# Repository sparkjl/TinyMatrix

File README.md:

## TinyMatrix点阵控制器
> 基于STM32F103 Microcontroller，HUB75接口的点阵控制器。可通过1 x 4按键、串口指令控制LED点阵屏显示。

### 1. 硬件
#### 1.1. HUB75接口定义
Led点阵板的HUB75接口，一般以DC3-16P牛角座封装形式接入。通常Led点阵板的左右两侧各有一个HUB75接口IN、OUT，以实现多块Led点阵板的组合扩展。HUB75接口中：R1、G1、B1分别为上半屏的红、绿、蓝控制信号，R2、G2、B2分别为下半屏的红、绿、蓝控制信号，A、B、C、D、E为行选择信号，CLK为数据时钟信号，LAT为数据锁存信号，OE为输出使能信号，GND为信号地。

<div align="center">
    
</div>

#### 1.2. HUB75扫描方式
将行扫描信号、行选择信号进行组合控制，就实现了整个Led点阵板的扫描显示。其具体实现过程如下：

<div align="center">
    
</div>

1. 从DATA_IN引脚（R1、G1、B1、R2、G2、B2）写入1 bit数据，将CLK引脚拉高产生上升沿将数据写入移位寄存器。如此循环m次将一行m bit数据传输至移位寄存器。
2. 将LATCH、<SPAN style="TEXT-DECORATION: overline">OE</SPAN>引脚拉高，m bit数据被从移位寄存器传输至缓存寄存器。同时缓存寄存器中数据被保持禁止从输出驱动器中输出，以使得在行选择信号切换时没有Led被点亮。
3. 切换并输出行选择信号。(初始状态时，第0行、第32行被选中。)
4. 将LATCH、<SPAN style="TEXT-DECORATION: overline">OE</SPAN>引脚拉低，m bit数据被从缓存寄存器传输至输出驱动器。同时移位寄存器中数据被锁存禁止从缓存寄存器中移出，此时对应选中行Led被点亮。

将以上步骤执行n/2次，便能实现m x n像素Led点阵板整个画面的扫描显示。如果扫描频率足够低，我们能看到逐行扫描显示的全过程：

<div align="center">
    
</div>

基于人眼视觉暂留效应（余晖效应），我们无法分辨刷新率在24Hz以上的动态画面。如果将扫描频率设置在60Hz，我们就能看到一幅完整的静态画面。而这也就是常见的显示器的基本原理。

最后，将Led点阵板上下两个部分的R1、G1、B1、R2、G2、B2控制信号进行组合，便能基于光学RGB模型实现全彩显示。

#### 1.3. Led Matrix控制板设计
了解了HUB75接口的控制原理，接下来进行Led Matrix控制板设计。

Led Matrix控制板设计思路如下：

<div align="center">
    
</div>

Led Matrix控制板的核心选择的是一款尺寸为 22.86mm x 53.34mm 的STM32最小系统板。其通过2 x 20Pin GPIO排针将板载STM32F103C8T6 MCU内集成的2x SPI、3x USART、2x I2C、1x CAN、37x I/O、2x ADC、4x Timer等硬件资源引出，以便外围扩展板调用。固件程序可通过SWD接口进行烧录和调试，可通过Reset键复位。板载2路Led灯，一路用于电源状态指示，一路用于程序状态指示。

<div align="center">
    
</div>

Led Matrix控制板设计1 x 4按键用于点阵控制器的参数设置。MCU相关GPIO经由74HC245连接至HUB75接口，以增加驱动电流并将驱动电压从3.3v转换至5.0v。外挂的W25Qxx系列SPI Flash用于存储系统参数和字库数据。UART串口可用于下载系统参数和字库数据，TTL-蓝牙模块、TTL-WiFi模块通过UART串口建立与MCU间的通讯以实现控制指令、显示数据的无线透传。Led Matrix控制板由外接电源适配器或内置锂离子电池提供系统电源，直流降压电路实现系统电源从12v-> 5v-> 3.3v电压转换以给各功能单元供电。

基于以上硬件需求，将Led Matrix控制板通过Eagle PCB设计如下。至于为什么是Eagle PCB，那是因为其小巧精悍、简单易用，丰富的元件库、精美的原理图、标准vector字体，无不透露着严谨精致。可惜的是，被Autodesk收购后的Eagle 9.6.2对于3D模型的预览编辑需要通过Fusion 360来实现。

<div align="center">
    
</div>
<div align="center">
    
</div>

### 2. 结构

Eagle 9.6.2不支持直接编辑3D封装，而只能通过Fusion 360以云托管元件库的方式导入。不想从Fusion 360中重构元件库，但又追求项目完整性，这怎么解决呢？那就选择KiCad，不仅支持3D封装的直接编辑，还能将Eagle的.sch原理图文件、.brd电路板文件转换成对应的KiCad格式文件。

使用KiCad将Led Matrix控制板的Eagle格式文件转换成KiCad格式文件，基于此添加编辑3D封装，导出Led Matrix控制板3D Step模型文件。

使用KiCad对MCU核心板重新进行layout，添加编辑3D封装，导出MCU核心板3D Step模型文件。

在Fusion 360中将Led Matrix控制板和MCU核心板进行零件装配、干涉检查。

在Fusion 360中将Led Matrix控制板设置为固定零件，以此为基准依据Led Matrix控制板的空间尺寸设计Led Matrix控制器的整体结构。选择亚克力板材作为外壳材质。顶部和底部亚克力板通过双通螺母柱进行连接，Led Matrix控制板和Led点阵板与底部亚克力板连接固定，四侧亚克力板与顶部和底部亚克力板通过卡扣扣合进行连接。

### 3. 软件
#### 3.1. RGB LED全彩显示
控制RGB LED实现全彩显示的传统方式是脉宽调制（Pulse Width Modulation），简称PWM。通过脉宽调制控制LED开关时间占比，进而实现RGB LED的亮度调节。如果对RGB模块中的三个LED进行此操作，则可以将红绿蓝三色按比例混合成对应的RGB全彩输出。对于Led Matrix Panel的全彩显示，PWM方式却不适用：这需要足够多的GPIO和定时器独立控制，需要消耗太多的硬件资源。那么我们如何通过软件方式予以解决呢？  

二进制编码调制（Binary Code Modulation），简称BCM。BCM利用二进制编码性质控制开关信号占空比。假设有一个位宽为4的二进制数：从其最低位向左移动至最高位依次表示1个时间切片、2个时间切片、4个时间切片、8个时间切片。将这4种时间切片混合，可产生分辨率为1/15的任意占空比。如此，位宽越大分辨率越高色彩越丰富。位宽为8的二进制数，可表示分辨率为1/255的任意占空比。但位宽越大，时间切片越小，意味着更高的CPU占用率。为更好地平衡系统性能和硬件资源，本项目中BCM位宽为4。例如，4位二进制数0101表示5/15或33.3%的占空比。

<div align="center">
    
</div>

Led Matrix Panel是逐行扫描显示的，所以需要预先将图像像素色彩转换成BCM值保存至图像缓冲区。创建4个图像缓冲区，以表示BCM位宽为4情况下的4种长度的时间切片中在扫描时间范围内哪些时间切片需要点亮LED。将这4个图像缓冲区构成的4个颜色通道Plane，进行图像融合就构成了一幅完整的静态图像。

<div align="center">
    
</div>

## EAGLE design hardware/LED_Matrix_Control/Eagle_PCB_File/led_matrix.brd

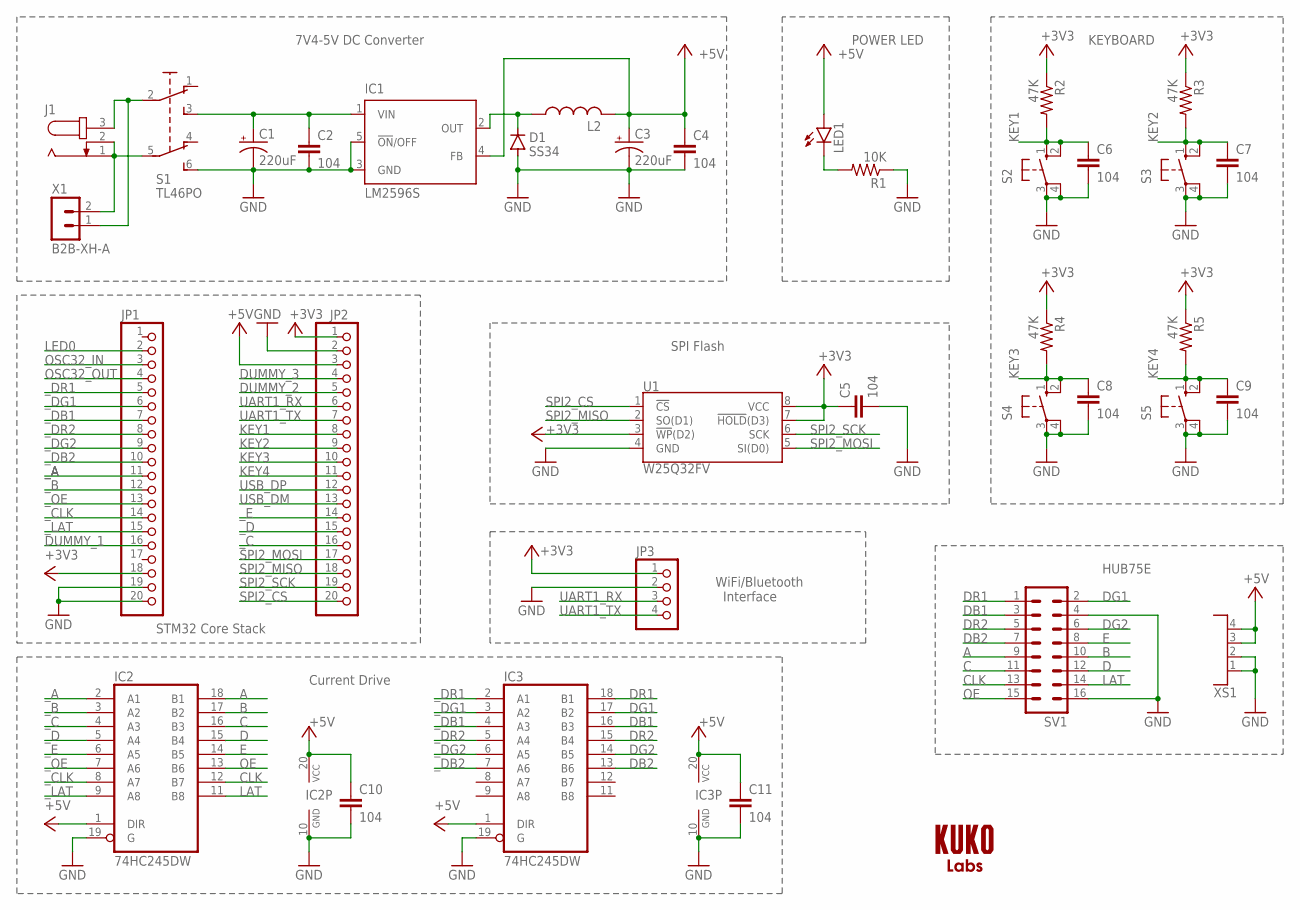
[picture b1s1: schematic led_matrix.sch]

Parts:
C1, C3: 220uF; 153CLV-0605
C2, C4, C5, C6, C7, C8, C9, C10, C11: 104; C0805
D1: SS34; DO214AC
IC1: LM2596S; TO263-5
IC2, IC3: 74HC245DW; SO20W
J1: JACK-PLUG0; SPC4077
JP1, JP2: PINHD-1X20; 1X20
JP3: PINHD-1X4; 1X04
L2: L-USL4532P; L4532P
LED1: LEDCHIP-LED0805; CHIP-LED0805
R1: 10K; R0805
R2, R3, R4, R5: 47K; R0805
S1: TL46PO; TL4XPO
S2, S3, S4, S5: 10-XX; B3F-10XX
SV1: ML16
U1: W25Q32FV; SOIC-8
U$1: LOGO
X1: B2B-XH-A
XS1: C4; NINIGI4C

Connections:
+3V3: C5.1, JP1.18, JP2.1, JP3.1, R2.1, R3.1, R4.1, R5.1, U1.3 (!WP!(D2)), U1.7 (!HOLD!(D3)), U1.8 (VCC)
+5V: C3.+, C4.1, C10.1, C11.1, IC1.4 (FB), IC2.1 (DIR), IC2.20 (VCC), IC3.1 (DIR), IC3.20 (VCC), JP2.3, L2.2, LED1.A, XS1.3, XS1.4
A: IC2.18 (B1), SV1.9
B: IC2.17 (B2), SV1.10
C: IC2.16 (B3), SV1.11
CLK: IC2.12 (B7), SV1.13
D: IC2.15 (B4), SV1.12
DB1: IC3.16 (B3), SV1.3
DB2: IC3.13 (B6), SV1.7
DG1: IC3.17 (B2), SV1.2
DG2: IC3.14 (B5), SV1.6
DR1: IC3.18 (B1), SV1.1
DR2: IC3.15 (B4), SV1.5
DUMMY_1: JP1.16
DUMMY_2: JP2.5
DUMMY_3: JP2.4
E: IC2.14 (B5), SV1.8
GND: C1.-, C2.2, C3.-, C4.2, C5.2, C6.2, C7.2, C8.2, C9.2, C10.2, C11.2, D1.A, IC1.3 (GND), IC1.5 (!ON!/OFF), IC2.10 (GND), IC2.19 (G), IC3.10 (GND), IC3.19 (G), JP1.19, JP1.20, JP2.2, JP3.2, R1.1, S1.6 (S1), S2.3, S2.4 (P1), S3.3, S3.4 (P1), S4.3, S4.4 (P1), S5.3, S5.4 (P1), SV1.4, SV1.16, U1.4 (GND), XS1.1, XS1.2
KEY1: C6.1, JP2.8, R2.2, S2.1 (S), S2.2 (S1)
KEY2: C7.1, JP2.9, R3.2, S3.1 (S), S3.2 (S1)
KEY3: C8.1, JP2.10, R4.2, S4.1 (S), S4.2 (S1)
KEY4: C9.1, JP2.11, R5.2, S5.1 (S), S5.2 (S1)
LAT: IC2.11 (B8), SV1.14
LED0: JP1.2
unnamed: J1.3, S1.2, X1.1
unnamed: J1.1, J1.2, S1.5 (P1), X1.2
unnamed: C1.+, C2.1, IC1.1 (VIN), S1.3 (S)
unnamed: D1.C, IC1.2 (OUT), L2.1
unnamed: LED1.C, R1.2
OE: IC2.13 (B6), SV1.15
OSC32_IN: JP1.3
OSC32_OUT: JP1.4
SPI2_CS: JP2.20, U1.1 (!CS!)
SPI2_MISO: JP2.18, U1.2 (SO(D1))
SPI2_MOSI: JP2.17, U1.5 (SI(D0))
SPI2_SCK: JP2.19, U1.6 (SCK)
UART1_RX: JP2.6, JP3.3
UART1_TX: JP2.7, JP3.4
USB_DM: JP2.13
USB_DP: JP2.12
_A: IC2.2 (A1), JP1.11
_B: IC2.3 (A2), JP1.12
_C: IC2.4 (A3), JP2.16
_CLK: IC2.8 (A7), JP1.14
_D: IC2.5 (A4), JP2.15
_DB1: IC3.4 (A3), JP1.7
_DB2: IC3.7 (A6), JP1.10
_DG1: IC3.3 (A2), JP1.6
_DG2: IC3.6 (A5), JP1.9
_DR1: IC3.2 (A1), JP1.5
_DR2: IC3.5 (A4), JP1.8
_E: IC2.6 (A5), JP2.14
_LAT: IC2.9 (A8), JP1.15
_OE: IC2.7 (A6), JP1.13

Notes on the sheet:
POWER LED
7V4-5V DC Converter
KEYBOARD
HUB75E
SPI Flash
STM32 Core Stack
Current Drive
WiFi/Bluetooth Interface

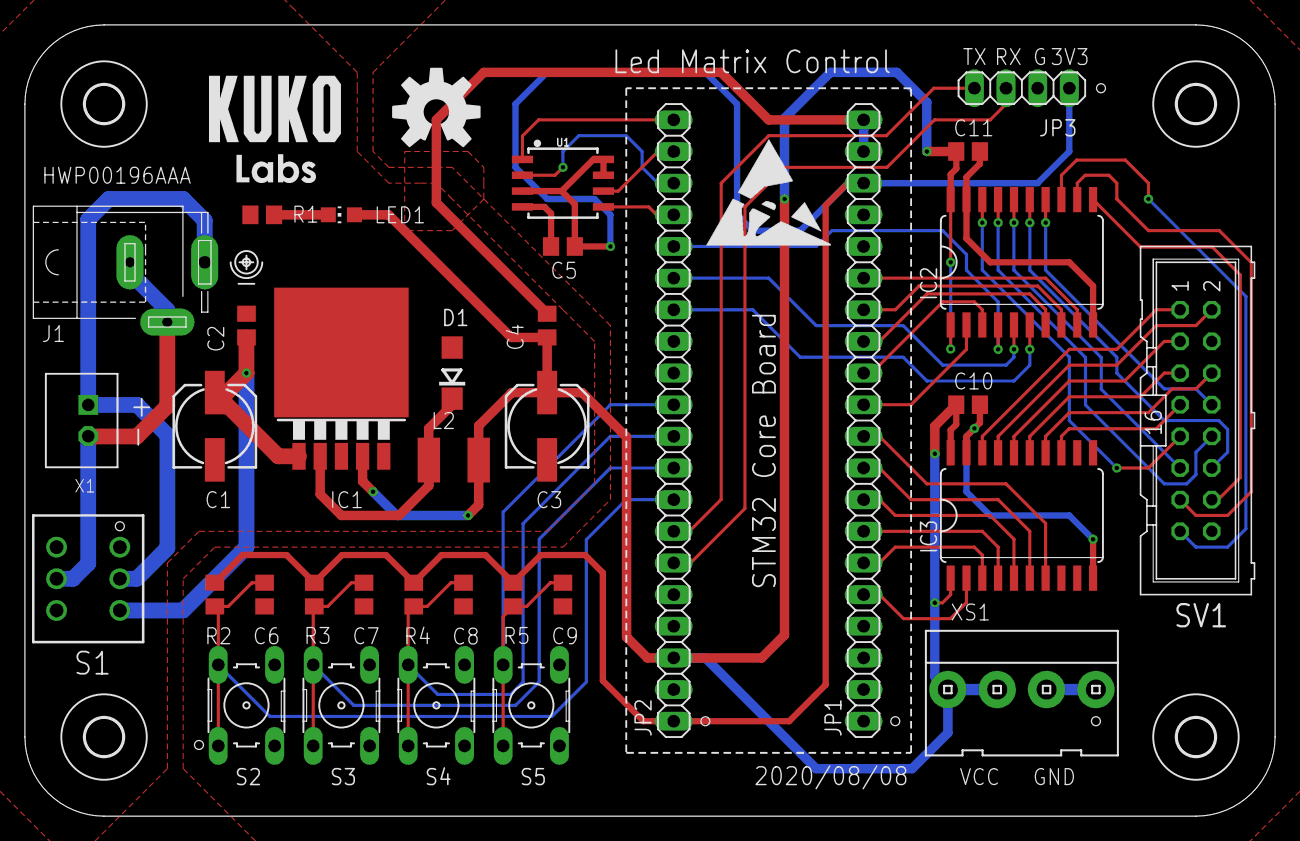
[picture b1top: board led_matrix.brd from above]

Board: 2 copper layers, 100.3 x 63.5 mm, 42 parts (0 on the bottom side), 46 nets.

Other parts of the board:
U$2, U$3, U$4, U$5: 3,0
U$6: ESD_10.00
U$7: OSHW-LOGO-L

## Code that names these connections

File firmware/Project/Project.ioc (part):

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Mcu.Name=STM32F103C(8-B)Tx
Mcu.Package=LQFP48
Mcu.UserName=STM32F103C8Tx
PA0-WKUP.GPIOParameters=GPIO_Label
PA0-WKUP.GPIO_Label=HUB75_DR1
PA0-WKUP.Signal=GPIO_Output
PA1.GPIOParameters=GPIO_Label
PA1.GPIO_Label=HUB75_DG1
PA1.Signal=GPIO_Output
PA10.GPIOParameters=GPIO_Label
PA10.GPIO_Label=HUB75_E
PA10.Signal=GPIO_Output
PA11.Mode=Device
PA11.Signal=USB_DM
PA12.Mode=Device
PA12.Signal=USB_DP
PA13.Mode=Serial_Wire
PA13.Signal=SYS_JTMS-SWDIO
PA14.Mode=Serial_Wire
PA14.Signal=SYS_JTCK-SWCLK
PA15.GPIOParameters=GPIO_Label
PA15.GPIO_Label=KEY_4
PA15.Signal=GPIO_Input
PA2.GPIOParameters=GPIO_Label
PA2.GPIO_Label=HUB75_DB1
PA2.Signal=GPIO_Output
PA3.GPIOParameters=GPIO_Label
PA3.GPIO_Label=HUB75_DR2
PA3.Signal=GPIO_Output
PA4.GPIOParameters=GPIO_Label
PA4.GPIO_Label=HUB75_DG2
PA4.Signal=GPIO_Output
PA5.GPIOParameters=GPIO_Label
PA5.GPIO_Label=HUB75_DB2
PA5.Signal=GPIO_Output
PA6.GPIOParameters=GPIO_Label
PA6.GPIO_Label=HUB75_A
PA6.Signal=GPIO_Output
PA7.GPIOParameters=GPIO_Label
PA7.GPIO_Label=HUB75_B
PA7.Signal=GPIO_Output
PA8.GPIOParameters=GPIO_Label
PA8.GPIO_Label=HUB75_C
PA8.Signal=GPIO_Output
PA9.GPIOParameters=GPIO_Label
PA9.GPIO_Label=HUB75_D
PA9.Signal=GPIO_Output
PB0.GPIOParameters=GPIO_Label
PB0.GPIO_Label=HUB75_OE
PB0.Signal=GPIO_Output
PB1.GPIOParameters=GPIO_Label
PB1.GPIO_Label=HUB75_CLK
PB1.Signal=GPIO_Output
PB10.GPIOParameters=GPIO_Label
PB10.GPIO_Label=HUB75_LAT
PB10.Signal=GPIO_Output
PB12.GPIOParameters=GPIO_Speed,PinState,GPIO_Label
PB12.GPIO_Label=SPI2_CS
PB12.GPIO_Speed=GPIO_SPEED_FREQ_HIGH
PB12.PinState=GPIO_PIN_SET
PB12.Signal=GPIO_Output
PB13.Mode=Full_Duplex_Master
PB13.Signal=SPI2_SCK
PB14.Mode=Full_Duplex_Master
PB14.Signal=SPI2_MISO
PB15.Mode=Full_Duplex_Master
PB15.Signal=SPI2_MOSI
PB3.GPIOParameters=GPIO_Label
PB3.GPIO_Label=KEY_3
PB3.Signal=GPIO_Input
PB4.GPIOParameters=GPIO_Label
PB4.GPIO_Label=KEY_2
PB4.Signal=GPIO_Input
PB5.GPIOParameters=GPIO_Label
PB5.GPIO_Label=KEY_1
PB5.Signal=GPIO_Input
PB6.Mode=Asynchronous
PB6.Signal=USART1_TX
PB7.Mode=Asynchronous
PB7.Signal=USART1_RX
PC13-TAMPER-RTC.GPIOParameters=GPIO_Label
PC13-TAMPER-RTC.GPIO_Label=LED1
PC13-TAMPER-RTC.Signal=GPIO_Output
PC14-OSC32_IN.Mode=LSE-External-Oscillator
PC14-OSC32_IN.Signal=RCC_OSC32_IN
PC15-OSC32_OUT.Mode=LSE-External-Oscillator
PC15-OSC32_OUT.Signal=RCC_OSC32_OUT
PD0-OSC_IN.Mode=HSE-External-Oscillator
PD0-OSC_IN.Signal=RCC_OSC_IN
PD1-OSC_OUT.Mode=HSE-External-Oscillator
PD1-OSC_OUT.Signal=RCC_OSC_OUT
RCC.SYSCLKFreq_VALUE=72000000
RCC.SYSCLKSource=RCC_SYSCLKSOURCE_PLLCLK
board=custom

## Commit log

2021-06-06 draft commit
2021-06-14 hub75 timing control via Timer TIM2
2021-06-20 long press KEY_ENTER to setup sys data
2021-06-20 change Menu MODE to Menu FONT: select&display, upgrade, erase font data
2021-07-11 add uart link protocol, modify crc16 check algorithm.
2021-07-18 uart link: restart uart rx before restart uart tx
2021-07-29 sort out
2021-07-31 font display upgrade
2021-08-02 add Freq Menu to set up display frequency and shift period
2021-08-14 Create images
2021-08-14 add image files
2021-08-14 revise README.md
2021-08-23 draft commit: driver for ICN2053
2021-08-29 driver for ICN2053/ICN2153
2021-08-31 adjust color channel
2021-09-04 disable OE output after initializing
2022-10-11 1.upgrade the firmware package to STM32Cube_FW_F1_V1.8.4 2.enlarge the capacity of heap and stack

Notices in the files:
parts and their libraries:
SparkFun-IC-Memory: Licensing: Creative Commons ShareAlike 4.0 International - https://creativecommons.org/licenses/by-sa/4.0
